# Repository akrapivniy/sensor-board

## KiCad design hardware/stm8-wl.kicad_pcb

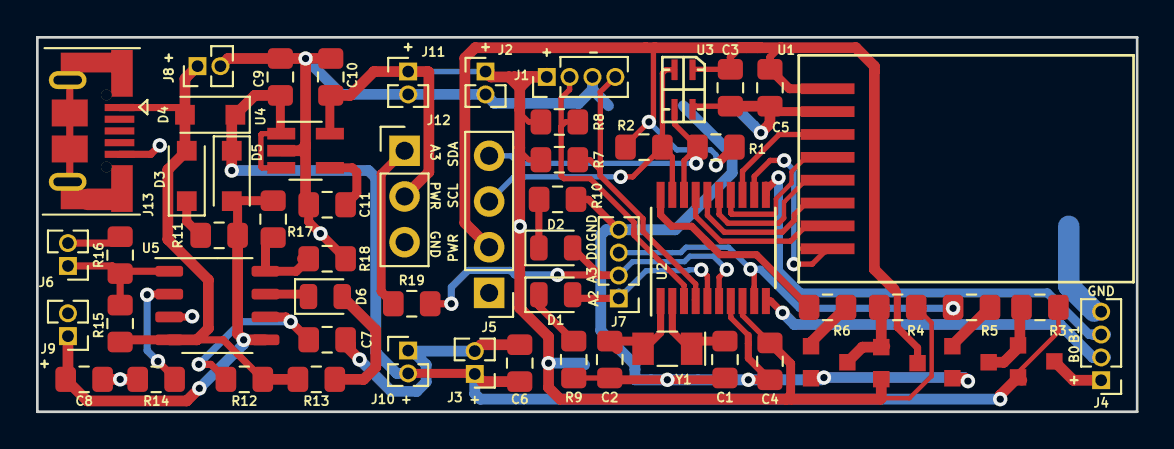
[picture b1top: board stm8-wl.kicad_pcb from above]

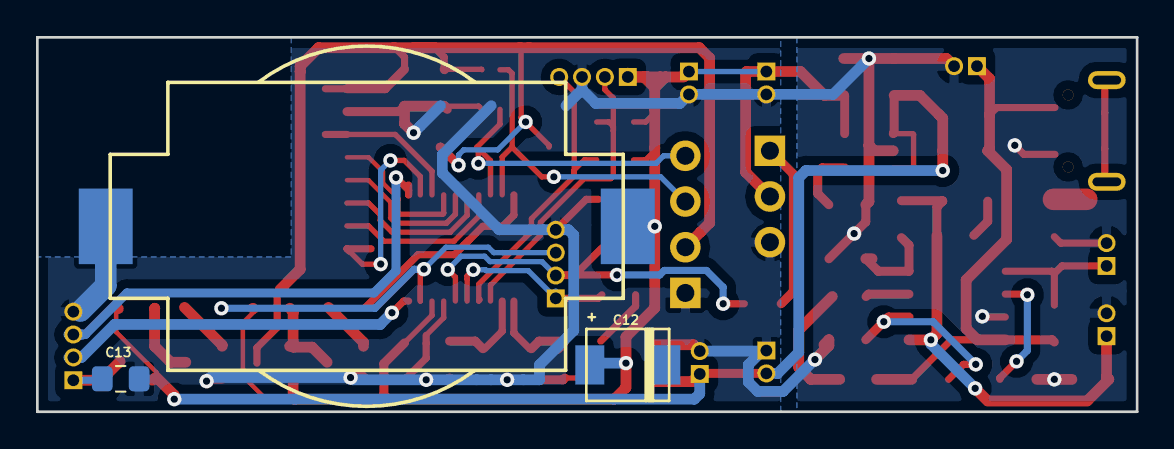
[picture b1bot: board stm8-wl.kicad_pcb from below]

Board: 2 copper layers, 61.1 x 20.8 mm, 62 parts (3 on the bottom side), 40 nets.

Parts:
BAT1: BS-7; CR2032-BS-6-1
C1, C2: 8pF; C_0805_2012Metric_Pad1.15x1.40mm_HandSolder
C3: 0.1uF; C_0805_2012Metric_Pad1.15x1.40mm_HandSolder
C4, C5, C7, C8, C9, C10, C11: 100nF; C_0805_2012Metric_Pad1.15x1.40mm_HandSolder
C6: 0,1uF; C_0805_2012Metric_Pad1.15x1.40mm_HandSolder
C12: CP; SMB
C13: 100uF; C_0805_2012Metric_Pad1.15x1.40mm_HandSolder
D1, D2, D6: LED; LED_0805_2012Metric
D3, D4, D5: D; D_SOD-123F
J1: Prog; PinHeader_1x04_P1.27mm_Vertical
J2: BAT; PinHeader_1x02_P1.27mm_Vertical
J3: PWR DEV; PinHeader_1x02_P1.27mm_Vertical
J4: DEV; PinHeader_1x04_P1.27mm_Vertical
J5: I2C; PinHeader_1x04_P2.54mm_Vertical
J6, J9: 3P BAT; PinHeader_1x02_P1.27mm_Vertical
J7: Ext. LED; PinHeader_1x04_P1.27mm_Vertical
J8: SOLAR; PinHeader_1x02_P1.27mm_Vertical
J10: PWD Dev; PinHeader_1x02_P1.27mm_Vertical
J11: PWRBoard; PinHeader_1x02_P1.27mm_Vertical
J12: PIR; PinHeader_1x03_P2.54mm_Vertical
J13: USB_B_Micro; USB_Micro-B
Q1, Q2: BC847BLT1G; SOT23-3
R1, R2, R19: 4.7K; R_0805_2012Metric_Pad1.15x1.40mm_HandSolder
R3, R4, R7, R8, R17: 100K; R_0805_2012Metric_Pad1.15x1.40mm_HandSolder
R5, R6, R9, R10, R11, R13, R15, R16: 1K; R_0805_2012Metric_Pad1.15x1.40mm_HandSolder
R12: 510K; R_0805_2012Metric_Pad1.15x1.40mm_HandSolder
R14: 2.4K; R_0805_2012Metric_Pad1.15x1.40mm_HandSolder
R18: 150K-274K; R_0805_2012Metric_Pad1.15x1.40mm_HandSolder
U1: NRF24L; NRF24L01SMD
U2: STM8L051F3P; TSSOP-20_4.4x6.5mm_P0.65mm
U3: SHTC3; DFN-4
U4: MIC5219; SOT-23-5_HandSoldering
U5: CN3085; SSOP-8_3.9x5.05mm_P1.27mm
VT1, VT2: NTS4101PT1G; SOT23-3
Y1: 32768Hz; Crystal_SMD_G8-2Pin_3.2x1.5mm_HandSoldering

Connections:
+3V3: BAT1.Pos, C4.1, C10.1, C12.1, J1.1, J2.1, J11.1, J12.2, R4.1, R7.1, R8.1, U2.8, U4.5, VT2.2
+3V8: C8.1, D5.2, J9.1, R11.1, R17.1, U5.5
+5VD: D3.2, D4.2, J8.1, J13.1, R12.1, R13.1, R15.2, U5.4
+9V: C6.1, C9.1, D4.1, D5.1, J3.1, J10.2, R3.1, U4.1, U4.3, VT1.2
/DeviceADC: J4.2, U2.10
/DeviceEnable: J7.3, R5.2, U2.9
/DevicePWM: J4.3, U2.11
/Enable: R6.2, U2.20
/I2C_SCL: J5.3, R2.2, U2.19, U3.2
/I2C_SDA: J5.4, R1.2, U2.18, U3.3
/LED0: D1.2, J7.1, U2.5
/LED1: D2.2, J7.2, R19.2, U2.6
/NRF_CE: U1.3, U2.13
/NRF_IRQ: U1.8, U2.12
/OSC32_IN: C2.1, U2.1, Y1.2
/OSC32_OUT: C1.1, U2.2, Y1.1
/PowerDevice: C13.1, J4.1, VT1.3
/PowerSensors: C3.1, C5.1, J5.2, R1.1, R2.1, U1.1, U3.1, VT2.3
/SPI_CLK: U1.5, U2.15
/SPI_CS: U1.4, U2.14
/SPI_MISO: U1.7, U2.17
/SPI_MOSI: U1.6, U2.16
/SWIM_DATA: J1.2, R8.2, U2.3
/SWIM_RESET: J1.4, R7.2, U2.4
GND: BAT1.Neg, C1.2, C2.2, C3.2, C4.2, C5.2, C6.2, C7.2, C8.2, C9.2, C10.2, C11.2, C12.2, C13.2, J1.3, J2.2, J3.2, J4.4, J5.1, J6.2, J7.4, J8.2, J9.2, J10.1, J11.2, J12.3, J13.5, Q1.2, Q2.2, R9.2, R10.2, R14.2, R16.2, R18.2, U1.2, U2.7, U3.4, U4.2, U5.3
unnamed: C7.1, R12.2, U5.6
unnamed: C11.1, U4.4
unnamed: D1.1, R9.1
unnamed: D2.1, R10.1
unnamed: D3.1, R11.2
unnamed: D6.1, U5.7
unnamed: D6.2, R13.2
unnamed: J6.1, R15.1, R16.1, U5.1
unnamed: J12.1, R19.1
unnamed: Q1.1, R5.1
unnamed: Q1.3, R3.2, VT1.1
unnamed: Q2.1, R6.1
unnamed: Q2.3, R4.2, VT2.1
unnamed: R14.1, U5.2
unnamed: R17.2, R18.1, U5.8

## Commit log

2021-04-25 Added KiCAD project for the sensor board
2021-05-01 Added RTC, I2C and SHTC3 drivers, Makefile and UUID generator
2021-05-01 sources: added ssd1306 display driver
